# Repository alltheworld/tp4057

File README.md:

# tp4056
TP4057 charger kicad schematics
Kicad version with tp4057 footprint and schematics

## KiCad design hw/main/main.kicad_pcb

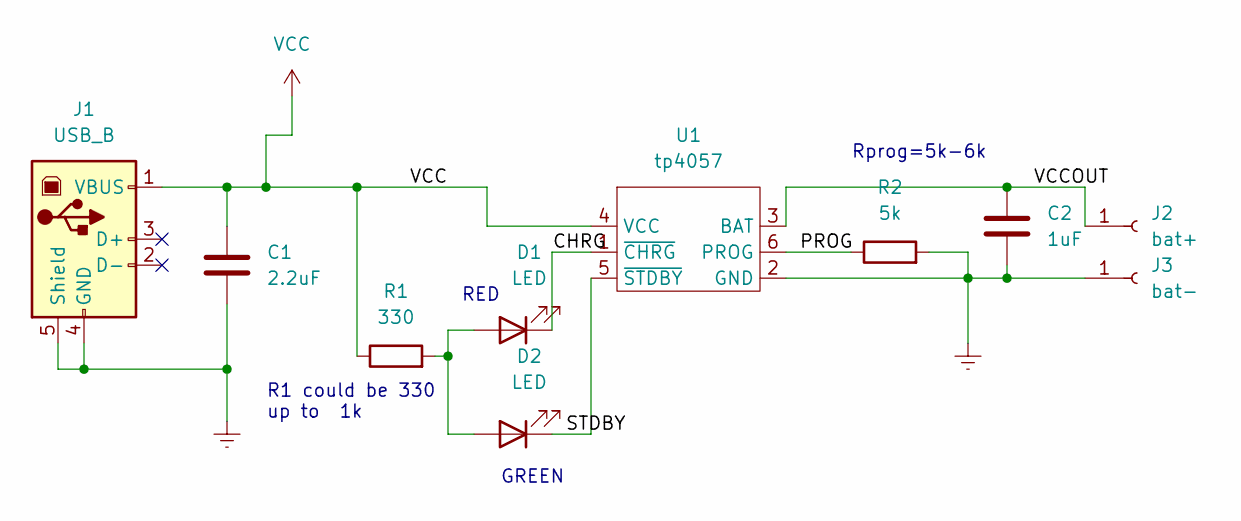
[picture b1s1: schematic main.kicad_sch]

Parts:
C1: 2.2uF; C_0603_1608Metric_Pad1.08x0.95mm_HandSolder
C2: 1uF; C_0603_1608Metric_Pad1.08x0.95mm_HandSolder
D1: LED; LED_D3.0mm
D2: LED; LED_D3.0mm_Clear
J1: USB_B; USB_B_Lumberg_2411_02_Horizontal
J2: bat+; PinHeader_1x01_P2.54mm_Vertical
J3: bat-; PinHeader_1x01_P2.54mm_Vertical
R1: 330; R_0603_1608Metric_Pad0.98x0.95mm_HandSolder
R2: 5k; R_Axial_DIN0207_L6.3mm_D2.5mm_P10.16mm_Horizontal
U1: tp4057; SOT-23-6_Handsoldering

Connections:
/CHRG: D1.1 (K), U1.1 (~CHRG)
/PROG: R2.1, U1.6 (PROG)
/STDBY: D2.1 (K), U1.5 (~STDBY)
/VCCOUT: C2.1, J2.1, U1.3 (BAT)
Earth: C1.2, C2.2, J1.4 (GND), J1.5 (Shield), J3.1, R2.2, U1.2 (GND)
unnamed: D1.2 (A), D2.2 (A), R1.2
VCC: C1.1, J1.1 (VBUS), R1.1, U1.4 (VCC)

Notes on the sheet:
R1 could be 330 up to 1k
RED
GREEN
Rprog=5k-6k

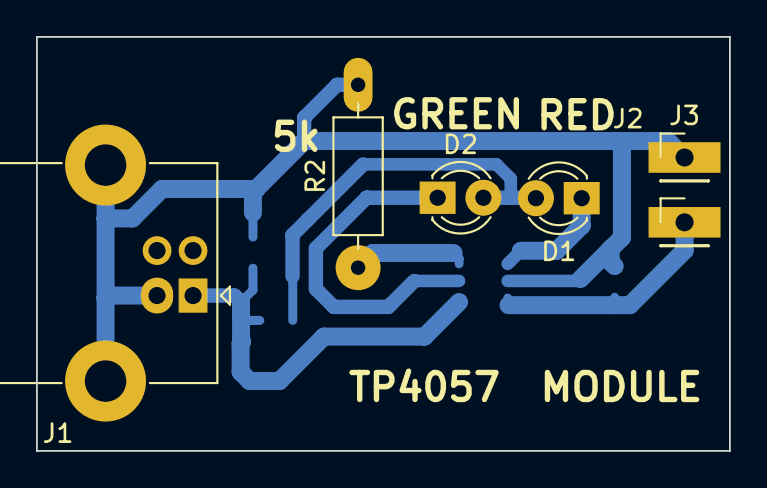
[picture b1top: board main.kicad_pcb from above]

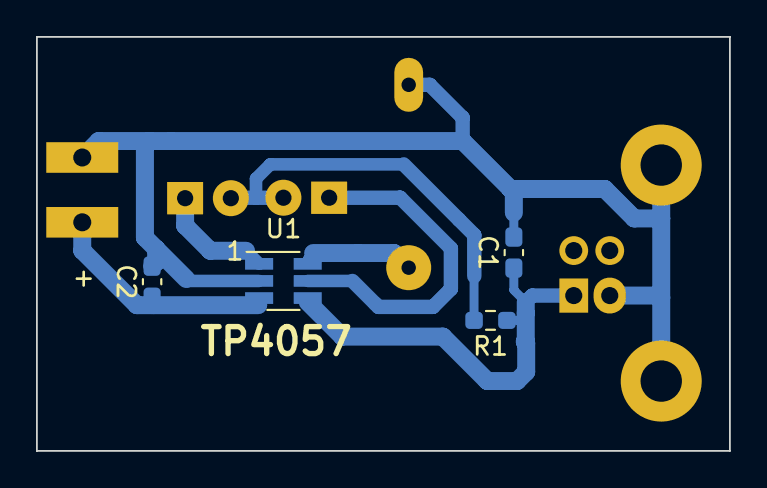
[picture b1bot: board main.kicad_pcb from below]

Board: 2 copper layers, 38.5 x 23.0 mm, 10 parts (4 on the bottom side), 7 nets.
